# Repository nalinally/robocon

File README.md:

ロボコンで使ったプログラムまとめておきます！ <br>
使ったマイコン <br>
・Nucleo f303k8 <br>
・Jetson Nano <br>
2021NHKfinal と 2021NHK がありますが、たぶん最新版は 2021NHK です

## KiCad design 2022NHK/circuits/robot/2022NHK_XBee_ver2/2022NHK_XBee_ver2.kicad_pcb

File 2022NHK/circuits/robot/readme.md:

# ロボットに乗せた回路です

たぶんいらないファイル(発注するために生成したやつとか)がたくさん入ってて見にくくてすみません

・2022NHK_Include ... メイン基板です メイン基板は3枚ありますが全部これです

・2022NHK_Convert ... サーボ用の信号線(6V)を5Vに変換します

・2022NHK_Relay ... 遠隔非常停止(受信側)のリレーを取り換え可能な感じにしました　そのためにリレーをdip化したやつです

・2022NHK_Source ... Tコネクタからの電源を5Vに降圧してUSB電源にします。各1.5Aずつしか流せないので注意

・2022NHK_XBee_Ver2 ... ロボットに乗せる遠隔非常停止(受信側) フォトカプラでリレーを駆動してます 当社比一番かっこいい回路

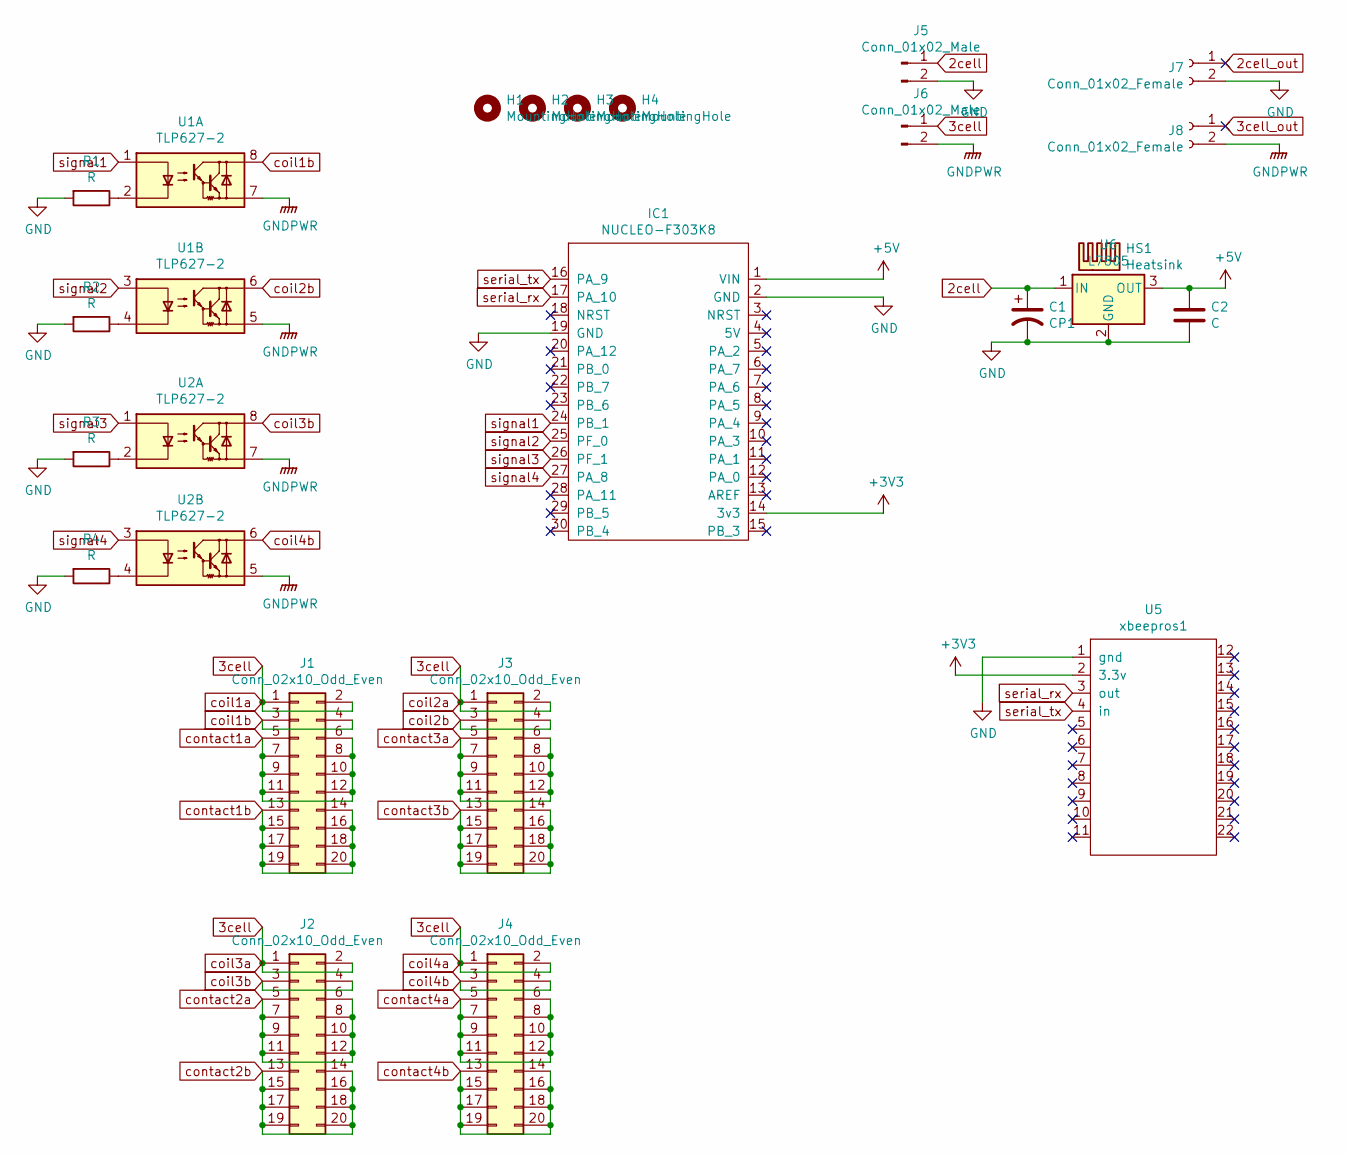
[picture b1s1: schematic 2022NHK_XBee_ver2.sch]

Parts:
C1: CP1; CP_Radial_D6.3mm_P2.50mm
C2: C; C_Disc_D4.7mm_W2.5mm_P5.00mm
H1, H2, H3, H4: MountingHole; MountingHole_3.2mm_M3_DIN965_Pad
HS1: Heatsink; Heatsink1
IC1: NUCLEO-F303K8
J1, J2, J3, J4: Conn_02x10_Odd_Even; PinSocket_2x10_P2.54mm_Vertical
J5, J6: Conn_01x02_Male; Connector_T_Male
J7, J8: Conn_01x02_Female; Connector_T_Female
R1, R2, R3, R4: R; R_Axial_DIN0309_L9.0mm_D3.2mm_P15.24mm_Horizontal
U1, U2: TLP627-2; DIP-8_W7.62mm
U5: xbeepros1; xbee_pro_s1
U6: L7805; TO-220F-3_Vertical

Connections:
2cell: C1.1, J5.1, U6.1 (IN)
2cell_out: J7.1
3cell: J1.1, J1.2, J2.1, J2.2, J3.1, J3.2, J4.1, J4.2, J6.1
3cell_out: J8.1
+3V3: IC1.14 (3v3), U5.2 (3.3v)
+5V: C2.1, IC1.1 (VIN), U6.3 (OUT)
GND: C1.2, C2.2, IC1.2 (GND), IC1.19 (GND), J5.2, J7.2, R1.2, R2.2, R3.2, R4.2, U5.1 (gnd), U6.2 (GND)
GNDPWR: J6.2, J8.2, U1.5, U1.7, U2.5, U2.7
unnamed: R1.1, U1.2
unnamed: R2.1, U1.4
unnamed: R3.1, U2.2
unnamed: R4.1, U2.4
coil1b: J1.3, J1.4, U1.8
coil2b: J3.3, J3.4, U1.6
coil3b: J2.3, J2.4, U2.8
coil4b: J4.3, J4.4, U2.6
contact1a: J1.5, J1.6, J1.7, J1.8, J1.9, J1.10, J1.11, J1.12
contact1b: J1.13, J1.14, J1.15, J1.16, J1.17, J1.18, J1.19, J1.20
contact2a: J2.5, J2.6, J2.7, J2.8, J2.9, J2.10, J2.11, J2.12
contact2b: J2.13, J2.14, J2.15, J2.16, J2.17, J2.18, J2.19, J2.20
contact3a: J3.5, J3.6, J3.7, J3.8, J3.9, J3.10, J3.11, J3.12
contact3b: J3.13, J3.14, J3.15, J3.16, J3.17, J3.18, J3.19, J3.20
contact4a: J4.5, J4.6, J4.7, J4.8, J4.9, J4.10, J4.11, J4.12
contact4b: J4.13, J4.14, J4.15, J4.16, J4.17, J4.18, J4.19, J4.20
serial_rx: IC1.17 (PA_10), U5.3 (out)
serial_tx: IC1.16 (PA_9), U5.4 (in)
signal1: IC1.24 (PB_1), U1.1
signal2: IC1.25 (PF_0), U1.3
signal3: IC1.26 (PF_1), U2.1
signal4: IC1.27 (PA_8), U2.3

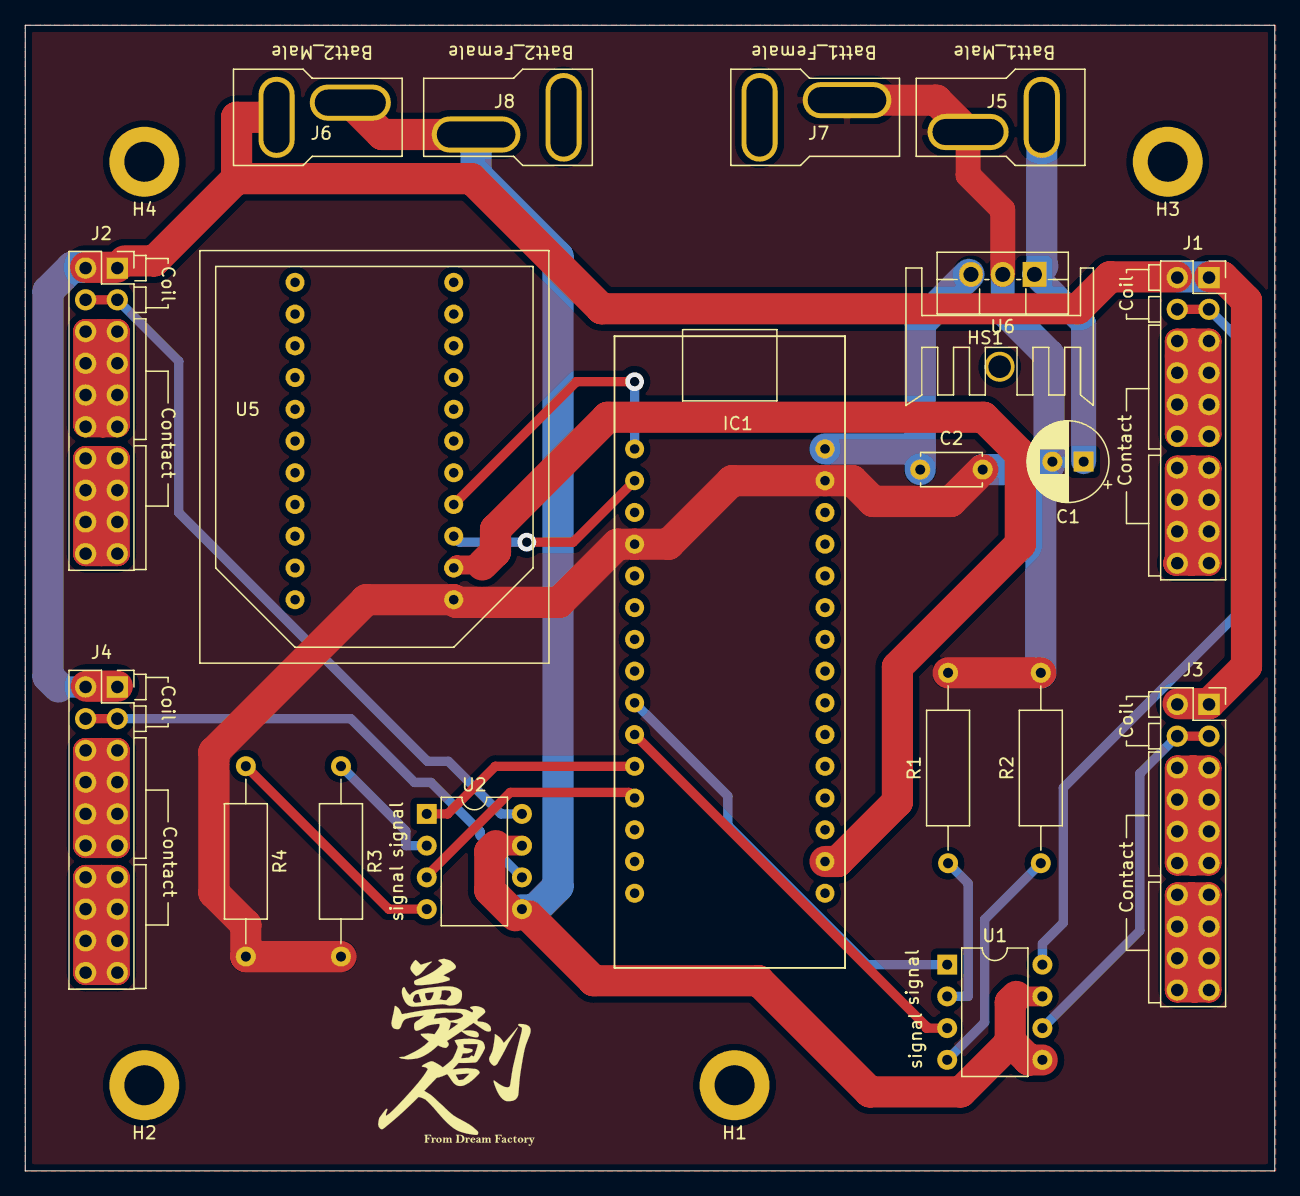
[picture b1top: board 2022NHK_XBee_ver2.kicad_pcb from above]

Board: 2 copper layers, 100.0 x 91.7 mm, 24 parts (0 on the bottom side), 28 nets.

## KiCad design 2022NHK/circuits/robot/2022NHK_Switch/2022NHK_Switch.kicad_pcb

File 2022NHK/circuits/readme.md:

# 回路がいるよ

controller ... コントローラに乗せる回路

robot ... ロボットに乗せる回路

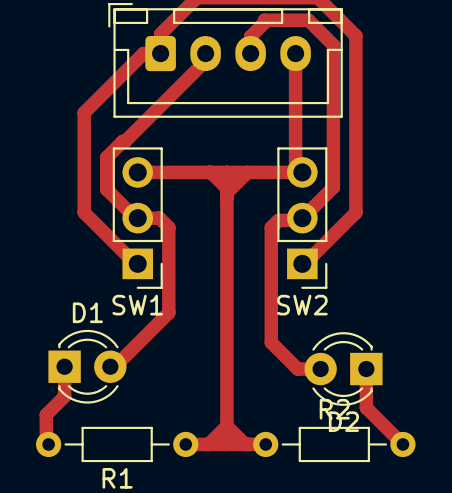
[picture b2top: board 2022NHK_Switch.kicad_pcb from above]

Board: 2 copper layers, 7 parts (0 on the bottom side), 6 nets.

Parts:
D1, D2: LED; LED_D3.0mm
J1: Conn_01x04_Male; JST_XH_B4B-XH-A_1x04_P2.50mm_Vertical
R1, R2: R; R_Axial_DIN0204_L3.6mm_D1.6mm_P7.62mm_Horizontal
SW1, SW2: SW_DPDT_x2; PinHeader_1x03_P2.54mm_Vertical

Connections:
5v: J1.1, SW1.1, SW2.1
GND: J1.4, R1.1, R2.1, SW1.3, SW2.3
unnamed: D1.1, R1.2
unnamed: D2.1, R2.2
out1: D1.2, J1.2, SW1.2
out2: D2.2, J1.3, SW2.2

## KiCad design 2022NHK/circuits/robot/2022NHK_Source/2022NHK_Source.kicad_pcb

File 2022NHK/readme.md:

# 2022年NHKロボコン(紙飛行機のやつ)のロボットの回路とプログラムを乗せます

circuits ... 回路

sources ... プログラム

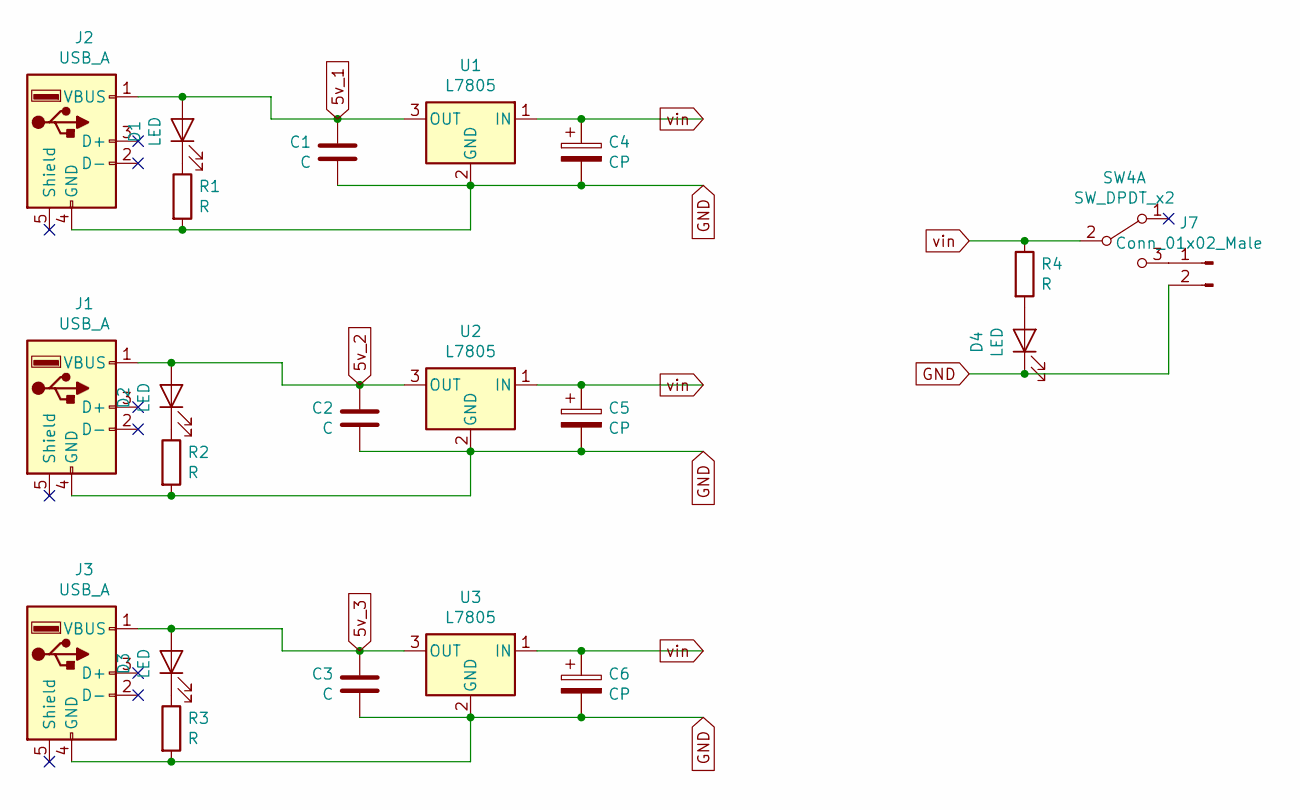
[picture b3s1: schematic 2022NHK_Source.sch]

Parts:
C1, C2, C3: C; C_Disc_D4.7mm_W2.5mm_P5.00mm
C4, C5, C6: CP; CP_Radial_D6.3mm_P2.50mm
D1, D2, D3, D4: LED; LED_D3.0mm
J1, J2, J3: USB_A; USB_A_Wuerth_61400826021_Horizontal_Stacked
J7: Conn_01x02_Male; Connector_T_Male
R1, R2, R3, R4: R; R_Axial_DIN0207_L6.3mm_D2.5mm_P7.62mm_Horizontal
SW4: SW_DPDT_x2; PinHeader_1x03_P2.54mm_Vertical
U1, U2, U3: L7805; TO-220F-3_Vertical

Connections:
5v_1: C1.1, D1.2 (A), J2.1 (VBUS), U1.3 (OUT)
5v_2: C2.1, D2.2 (A), J1.1 (VBUS), U2.3 (OUT)
5v_3: C3.1, D3.2 (A), J3.1 (VBUS), U3.3 (OUT)
GND: C1.2, C2.2, C3.2, C4.2, C5.2, C6.2, D4.1 (K), J1.4 (GND), J2.4 (GND), J3.4 (GND), J7.2, R1.2, R2.2, R3.2, U1.2 (GND), U2.2 (GND), U3.2 (GND)
unnamed: D1.1 (K), R1.1
unnamed: D2.1 (K), R2.1
unnamed: D3.1 (K), R3.1
unnamed: D4.2 (A), R4.2
unnamed: J7.1, SW4.3 (C)
vin: C4.1, C5.1, C6.1, R4.1, SW4.2 (B), U1.1 (IN), U2.1 (IN), U3.1 (IN)

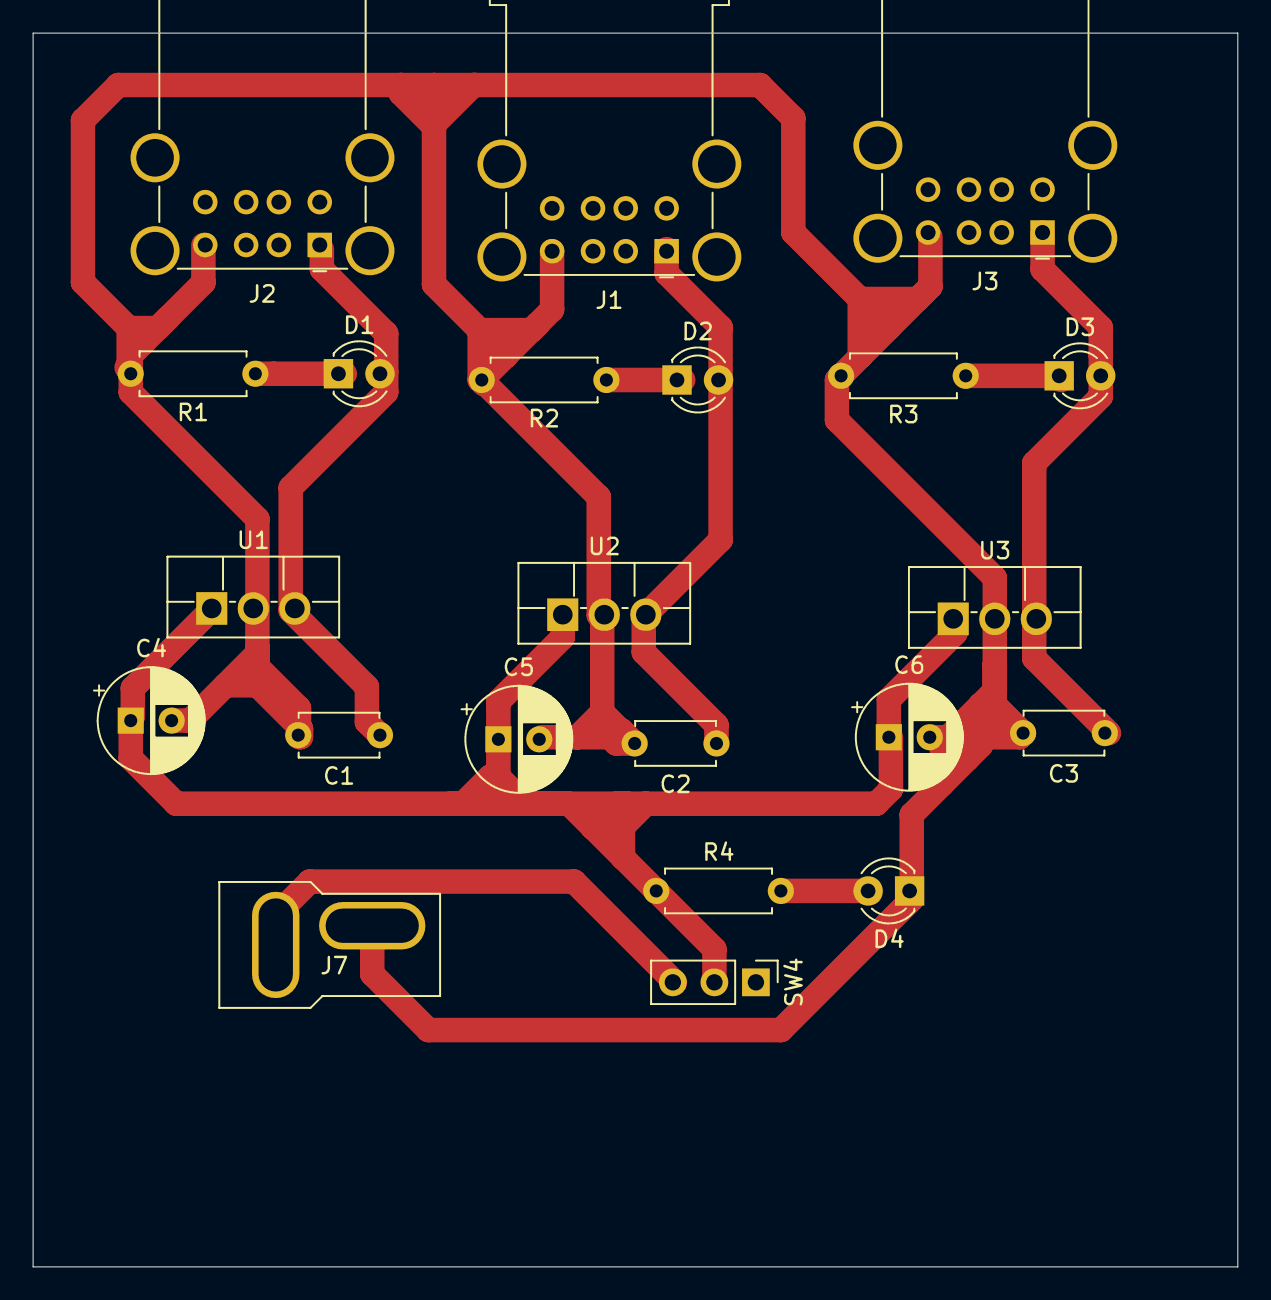
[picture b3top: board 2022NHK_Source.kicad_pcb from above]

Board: 2 copper layers, 73.7 x 75.4 mm, 22 parts (0 on the bottom side), 10 nets.

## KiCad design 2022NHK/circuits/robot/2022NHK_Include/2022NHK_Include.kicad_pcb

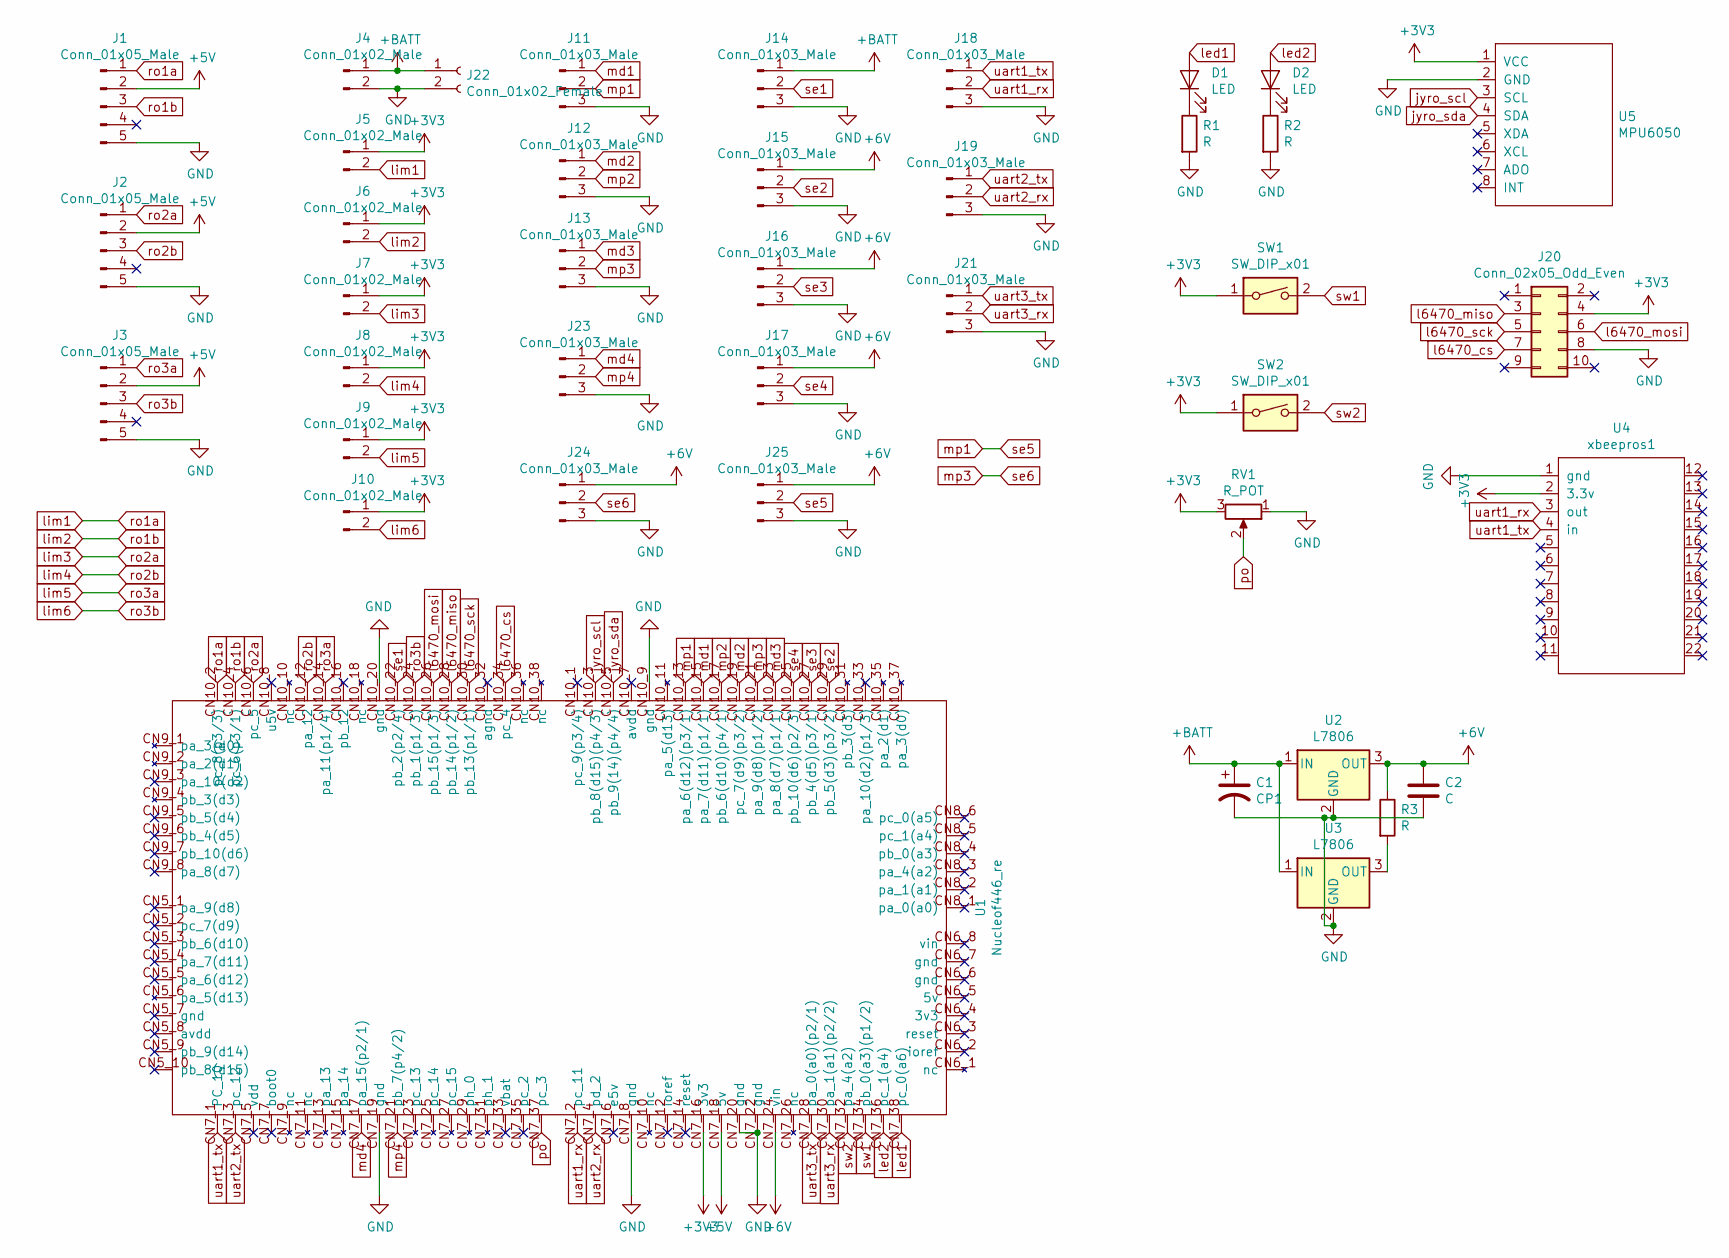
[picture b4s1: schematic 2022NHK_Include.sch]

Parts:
C1: CP1; CP_Radial_D7.5mm_P2.50mm
C2: C; C_Axial_L3.8mm_D2.6mm_P7.50mm_Horizontal
D1, D2: LED; LED_D3.0mm
J1, J2, J3: Conn_01x05_Male; JST_XH_B5B-XH-A_1x05_P2.50mm_Vertical
J4: Conn_01x02_Male; Connector_T_Male
J5, J6, J7, J8, J9, J10: Conn_01x02_Male; JST_XH_S2B-XH-A_1x02_P2.50mm_Horizontal
J11, J12, J13, J14, J15, J16, J17, J23: Conn_01x03_Male; JST_XH_S3B-XH-A_1x03_P2.50mm_Horizontal
J18, J19, J21, J24, J25: Conn_01x03_Male; JST_XH_B3B-XH-A_1x03_P2.50mm_Vertical
J20: Conn_02x05_Odd_Even; PinHeader_2x05_P2.54mm_Vertical
J22: Conn_01x02_Female; Connector_T_Female
R1, R2, R3: R; R_Axial_DIN0204_L3.6mm_D1.6mm_P7.62mm_Horizontal
RV1: R_POT; Potentiometer_Bourns_PTV09A-1_Single_Vertical
SW1, SW2: SW_DIP_x01; SW_Toggle_2.54mm
U1: Nucleof446_re; MODULE_NUCLEO_F446RE
U2, U3: L7806; NJM7805FA
U4: xbeepros1; xbee_pro_s1
U5: MPU6050; GY=521

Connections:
+3V3: J5.1, J6.1, J7.1, J8.1, J9.1, J10.1, J20.4, RV1.3, SW1.1, SW2.1, U1.CN7_16 (3v3), U4.2 (3.3v), U5.1 (VCC)
+5V: J1.2, J2.2, J3.2, U1.CN7_18 (5v)
+6V: C2.1, J15.1, J16.1, J17.1, J24.1, J25.1, R3.1, U1.CN7_24 (vin), U2.3 (OUT)
+BATT: C1.1, J4.1, J14.1, J22.1, U2.1 (IN), U3.1 (IN)
GND: C1.2, C2.2, J1.5, J2.5, J3.5, J4.2, J11.3, J12.3, J13.3, J14.3, J15.3, J16.3, J17.3, J18.3, J19.3, J20.8, J21.3, J22.2, J23.3, J24.3, J25.3, R1.2, R2.2, RV1.1, U1.CN7_8 (gnd), U1.CN7_19 (gnd), U1.CN7_20 (gnd), U1.CN7_22 (gnd), U1.CN10_9 (gnd), U1.CN10_20 (gnd), U2.2 (GND), U3.2 (GND), U4.1 (gnd), U5.2 (GND)
unnamed: D1.1 (K), R1.1
unnamed: D2.1 (K), R2.1
unnamed: R3.2, U3.3 (OUT)
jyro_scl: U1.CN10_3 (pb_8(d15)(p4/3)), U5.3 (SCL)
jyro_sda: U1.CN10_5 (pb_9(14)(p4/4)), U5.4 (SDA)
l6470_cs: J20.7, U1.CN10_34 (pc_4)
l6470_miso: J20.3, U1.CN10_28 (pb_14(p1/2))
l6470_mosi: J20.6, U1.CN10_26 (pb_15(p1/3))
l6470_sck: J20.5, U1.CN10_30 (pb_13(p1/1))
led1: D1.2 (A), U1.CN7_38 (pc_0(a6))
led2: D2.2 (A), U1.CN7_36 (pc_1(a4))
lim1: J1.1, J5.2, U1.CN10_2 (pc_8(p3/3))
lim2: J1.3, J6.2, U1.CN10_4 (pc_6(p3/1))
lim3: J2.1, J7.2, U1.CN10_6 (pc_5)
lim4: J2.3, J8.2, U1.CN10_12 (pa_12)
lim5: J3.1, J9.2, U1.CN10_14 (pa_11(p1/4))
lim6: J3.3, J10.2, U1.CN10_24 (pb_1(p1/3))
md1: J11.1, U1.CN10_15 (pa_7(d11)(p1/1))
md2: J12.1, U1.CN10_19 (pc_7(d9)(p3/2))
md3: J13.1, U1.CN10_23 (pa_8(d7)(p1/1))
md4: J23.1, U1.CN7_17 (pa_15(p2/1))
mp1: J11.2, J25.2, U1.CN10_13 (pa_6(d12)(p3/1))
mp2: J12.2, U1.CN10_17 (pb_6(d10)(p4/1))
mp3: J13.2, J24.2, U1.CN10_21 (pa_9(d8)(p1/2))
mp4: J23.2, U1.CN7_21 (pb_7(p4/2))
po: RV1.2, U1.CN7_37 (pc_3)
se1: J14.2, U1.CN10_22 (pb_2(p2/4))
se2: J15.2, U1.CN10_29 (pb_5(d3)(p3/2))
se3: J16.2, U1.CN10_27 (pb_4(d5)(p3/1))
se4: J17.2, U1.CN10_25 (pb_10(d6)(p2/3))
sw1: SW1.2, U1.CN7_34 (pb_0(a3)(p1/2))
sw2: SW2.2, U1.CN7_32 (pa_4(a2))
uart1_rx: J18.2, U1.CN7_2 (pc_11), U4.3 (out)
uart1_tx: J18.1, U1.CN7_1 (PC_10), U4.4 (in)
uart2_rx: J19.2, U1.CN7_4 (pd_2)
uart2_tx: J19.1, U1.CN7_3 (pc_12)
uart3_rx: J21.2, U1.CN7_30 (pa_1(a1)(p2/2))
uart3_tx: J21.1, U1.CN7_28 (pa_0(a0)(p2/1))

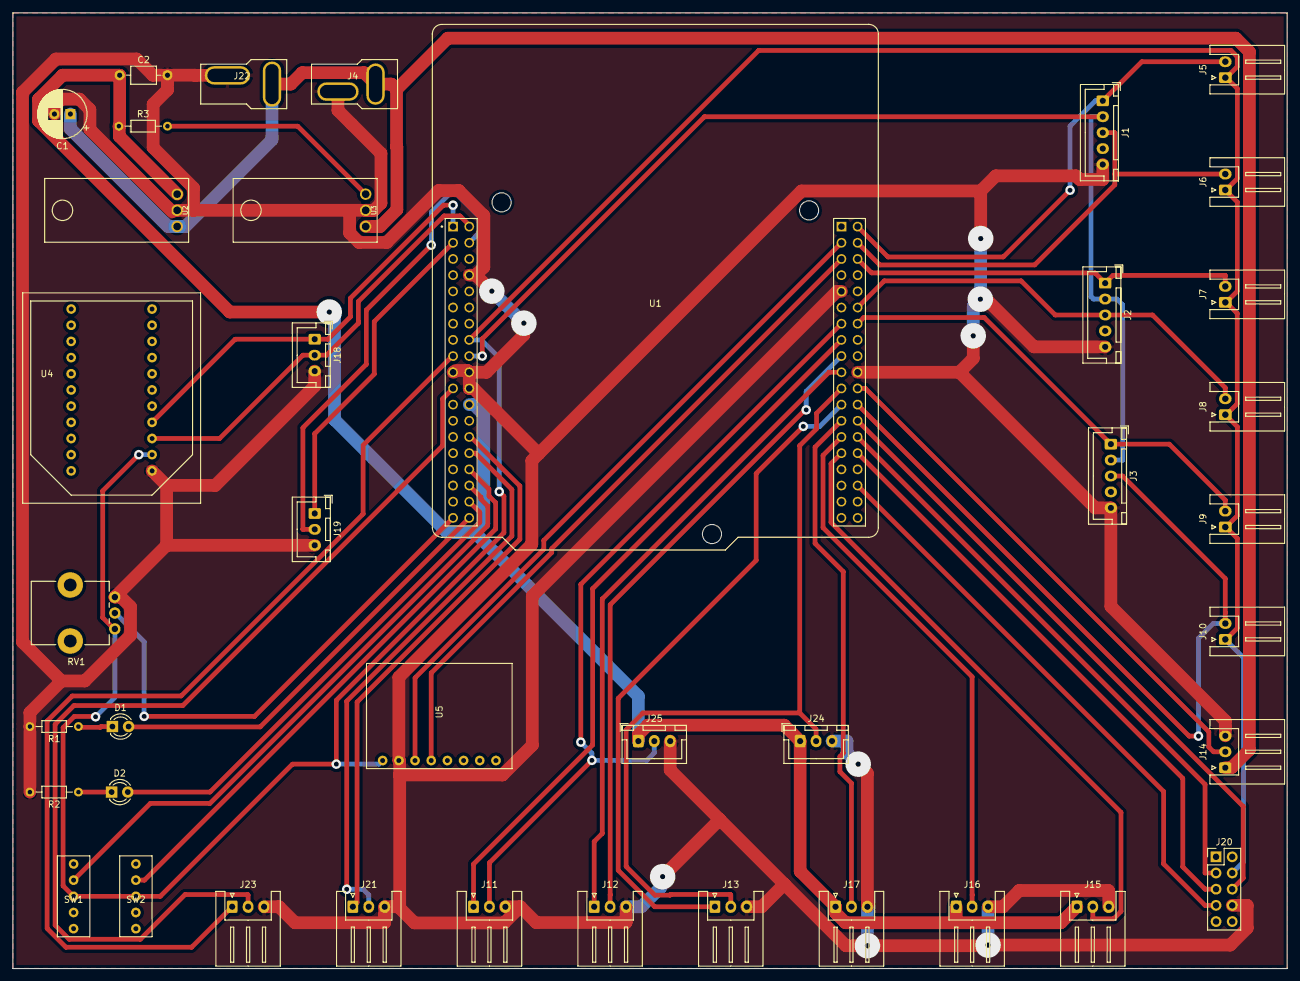
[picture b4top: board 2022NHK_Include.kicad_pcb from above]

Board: 2 copper layers, 200.0 x 150.0 mm, 40 parts (0 on the bottom side), 43 nets.

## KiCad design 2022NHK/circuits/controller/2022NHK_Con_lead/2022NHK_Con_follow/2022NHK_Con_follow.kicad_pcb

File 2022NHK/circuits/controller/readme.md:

# コントローラに乗せる用の回路です

・2022NHK_Con_Lead ... 親機基板

・2022NHK_Con_Follow ... 子機基板

・2022NHK_Switch ... 右手、左手の動かすかどうかの切り替え基板

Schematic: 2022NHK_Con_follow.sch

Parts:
C1: CP1; CP_Radial_D6.3mm_P2.50mm
C2: C; C_Disc_D4.3mm_W1.9mm_P5.00mm
D1: LED; LED_D3.0mm
IC1: NUCLEO-F303K8
J2, J5, J6, J8, J9, J10: Conn_01x05_Male; JST_XH_S5B-XH-A_1x05_P2.50mm_Horizontal
J3: Conn_01x02_Male; Connector_T_Male
J4: Conn_01x02_Female; Connector_T_Female
J7: Conn_01x03_Male; JST_XH_S3B-XH-A_1x03_P2.50mm_Horizontal
J11: Conn_01x02_Male; JST_XH_S2B-XH-A_1x02_P2.50mm_Horizontal
R1: R; R_Axial_DIN0204_L3.6mm_D1.6mm_P7.62mm_Horizontal
U1: L7805; NJM7805FA

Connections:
2a: IC1.20, J5.3
2b: IC1.27, J5.1
3a: IC1.28, J8.3
3b: IC1.12, J8.1
4a: IC1.6, J2.3
4b: IC1.7, J2.1
5a: IC1.8, J6.3
5b: IC1.9, J6.1
5v_in: C2.1, IC1.1, U1.3 (OUT)
5v_out: IC1.4, J2.2, J5.2, J6.2, J8.2, J9.2
6a: IC1.10, J9.3
6b: IC1.11, J9.1
+3V3: IC1.14, J10.1
+BATT: C1.1, J3.1, J4.1, U1.1 (IN)
GND: C1.2, C2.2, IC1.2, IC1.19, J2.5, J3.2, J4.2, J5.5, J6.5, J7.3, J8.5, J9.5, J10.2, J11.2, R1.2, U1.2 (GND)
unnamed: D1.1 (K), R1.1
bt1: IC1.29, J10.3
bt2: IC1.30, J10.4
bt3: IC1.15, J10.5
led1: D1.2 (A), IC1.24, J11.1
uart_rx: IC1.17, IC1.22, J7.2
uart_tx: IC1.16, IC1.23, J7.1

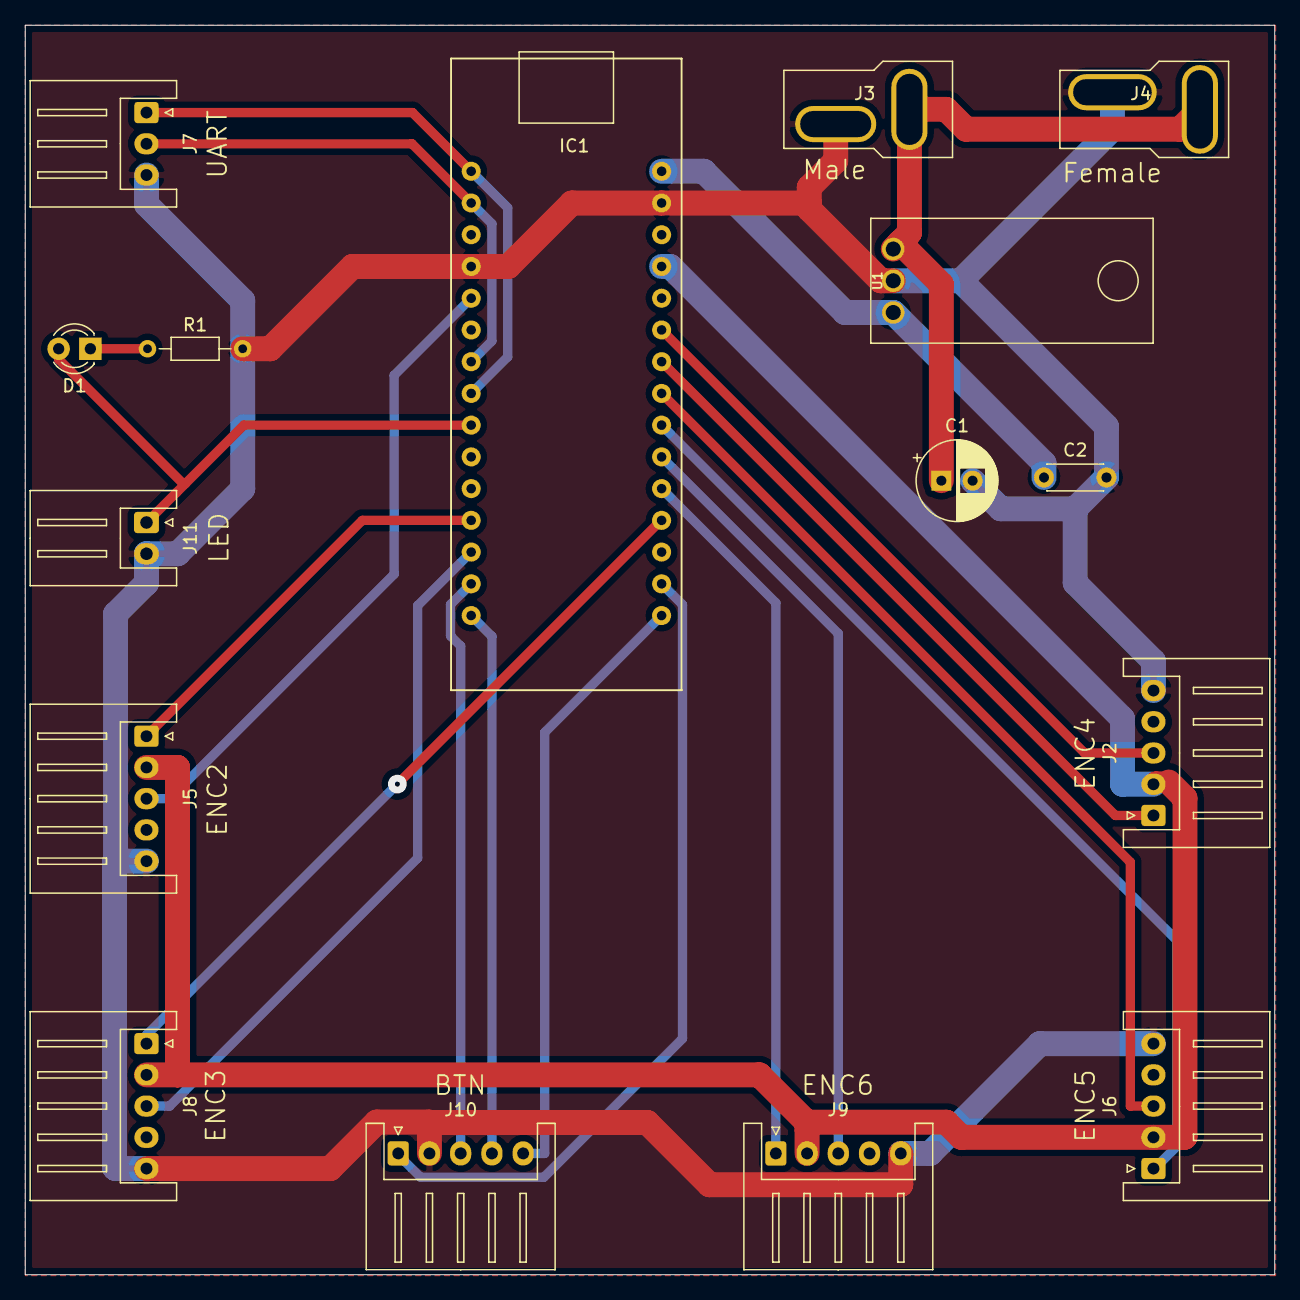
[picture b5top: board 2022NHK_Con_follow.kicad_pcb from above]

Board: 2 copper layers, 100.0 x 100.0 mm, 16 parts (0 on the bottom side), 22 nets.

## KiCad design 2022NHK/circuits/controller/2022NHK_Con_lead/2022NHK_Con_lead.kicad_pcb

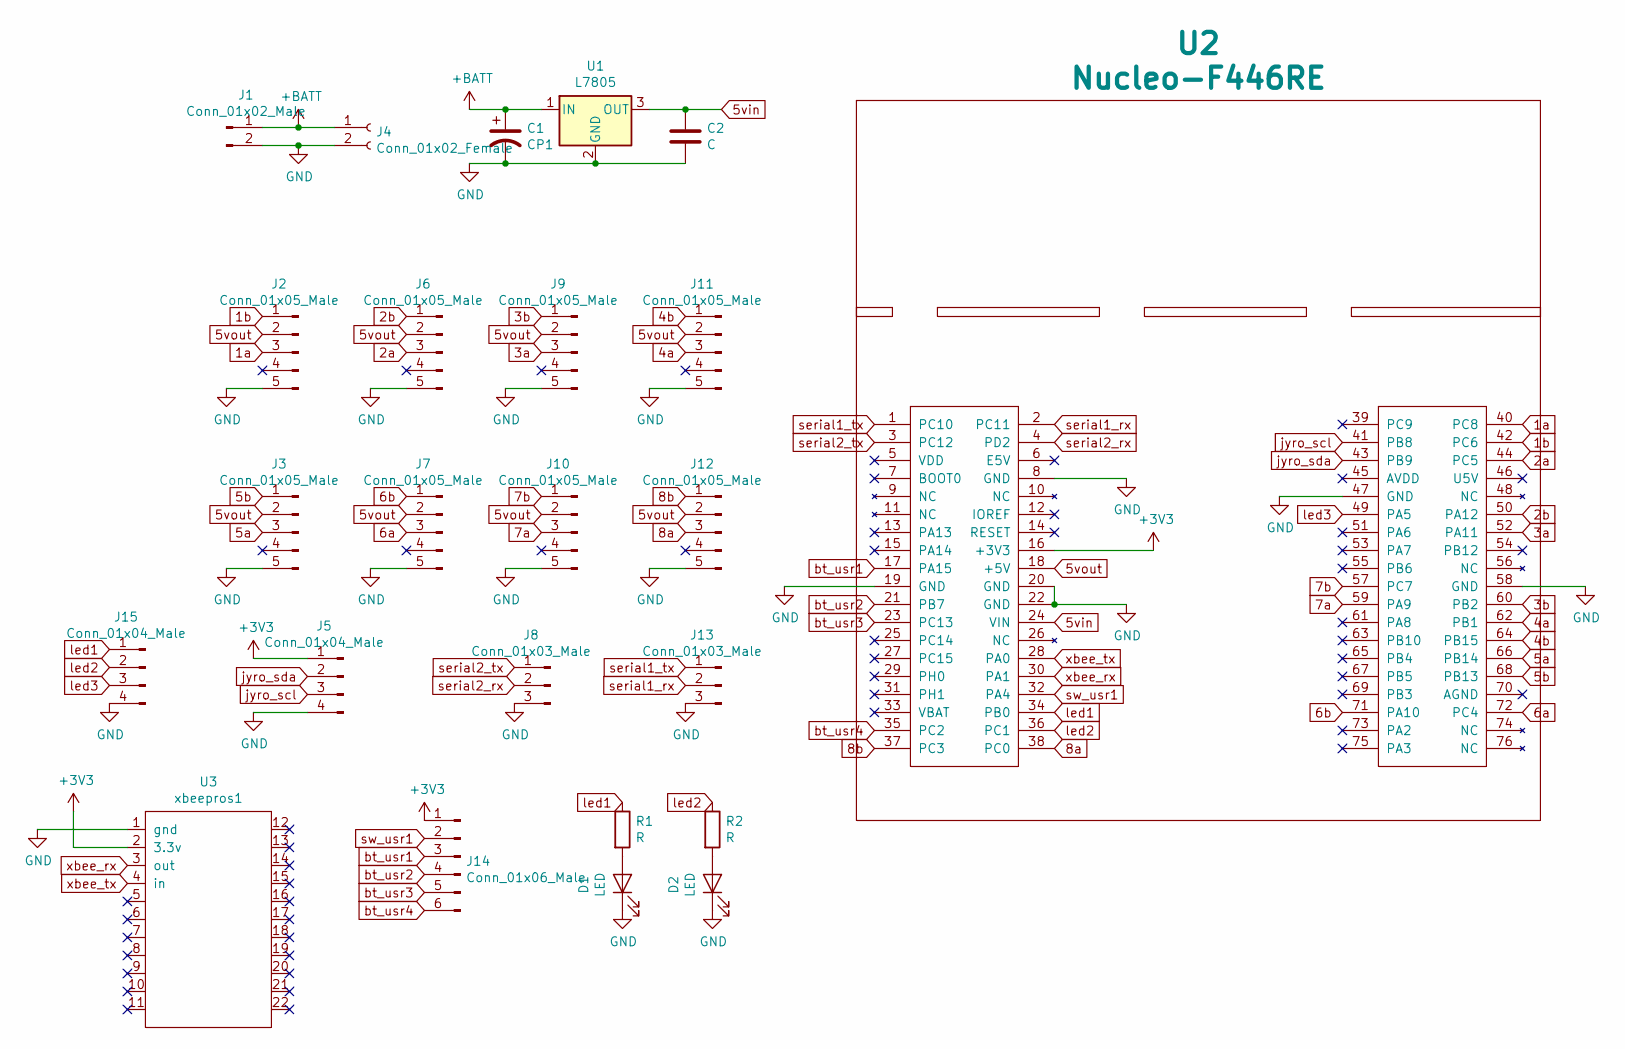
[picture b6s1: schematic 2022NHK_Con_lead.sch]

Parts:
C1: CP1; CP_Radial_D6.3mm_P2.50mm
C2: C; C_Axial_L3.8mm_D2.6mm_P7.50mm_Horizontal
D1, D2: LED; LED_D3.0mm
J1: Conn_01x02_Male; Connector_T_Male
J2, J3, J6, J7, J9, J10, J11, J12: Conn_01x05_Male; JST_XH_S5B-XH-A_1x05_P2.50mm_Horizontal
J4: Conn_01x02_Female; Connector_T_Female
J5, J15: Conn_01x04_Male; JST_XH_S4B-XH-A_1x04_P2.50mm_Horizontal
J8, J13: Conn_01x03_Male; JST_XH_S3B-XH-A_1x03_P2.50mm_Horizontal
J14: Conn_01x06_Male; JST_XH_S6B-XH-A_1x06_P2.50mm_Horizontal
R1, R2: R; R_Axial_DIN0204_L3.6mm_D1.6mm_P7.62mm_Horizontal
U1: L7805; NJM7805FA
U2: Nucleo-F446RE; MODULE_NUCLEO_F446RE
U3: xbeepros1; xbee_pro_s1

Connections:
1a: J2.3, U2.40 (PC8)
1b: J2.1, U2.42 (PC6)
2a: J6.3, U2.44 (PC5)
2b: J6.1, U2.50 (PA12)
3a: J9.3, U2.52 (PA11)
3b: J9.1, U2.60 (PB2)
4a: J11.3, U2.62 (PB1)
4b: J11.1, U2.64 (PB15)
5a: J3.3, U2.66 (PB14)
5b: J3.1, U2.68 (PB13)
5vin: C2.1, U1.3 (OUT), U2.24 (VIN)
5vout: J2.2, J3.2, J6.2, J7.2, J9.2, J10.2, J11.2, J12.2, U2.18 (+5V)
6a: J7.3, U2.72 (PC4)
6b: J7.1, U2.71 (PA10)
7a: J10.3, U2.59 (PA9)
7b: J10.1, U2.57 (PC7)
8a: J12.3, U2.38 (PC0)
8b: J12.1, U2.37 (PC3)
+3V3: J5.1, J14.1, U2.16 (+3V3), U3.2 (3.3v)
+BATT: C1.1, J1.1, J4.1, U1.1 (IN)
GND: C1.2, C2.2, D1.1 (K), D2.1 (K), J1.2, J2.5, J3.5, J4.2, J5.4, J6.5, J7.5, J8.3, J9.5, J10.5, J11.5, J12.5, J13.3, J15.4, U1.2 (GND), U2.8 (GND), U2.19 (GND), U2.20 (GND), U2.22 (GND), U2.47 (GND), U2.58 (GND), U3.1 (gnd)
unnamed: D1.2 (A), R1.2
unnamed: D2.2 (A), R2.2
bt_usr1: J14.3, U2.17 (PA15)
bt_usr2: J14.4, U2.21 (PB7)
bt_usr3: J14.5, U2.23 (PC13)
bt_usr4: J14.6, U2.35 (PC2)
jyro_scl: J5.3, U2.41 (PB8)
jyro_sda: J5.2, U2.43 (PB9)
led1: J15.1, R1.1, U2.34 (PB0)
led2: J15.2, R2.1, U2.36 (PC1)
led3: J15.3, U2.49 (PA5)
serial1_rx: J13.2, U2.2 (PC11)
serial1_tx: J13.1, U2.1 (PC10)
serial2_rx: J8.2, U2.4 (PD2)
serial2_tx: J8.1, U2.3 (PC12)
sw_usr1: J14.2, U2.32 (PA4)
xbee_rx: U2.30 (PA1), U3.3 (out)
xbee_tx: U2.28 (PA0), U3.4 (in)

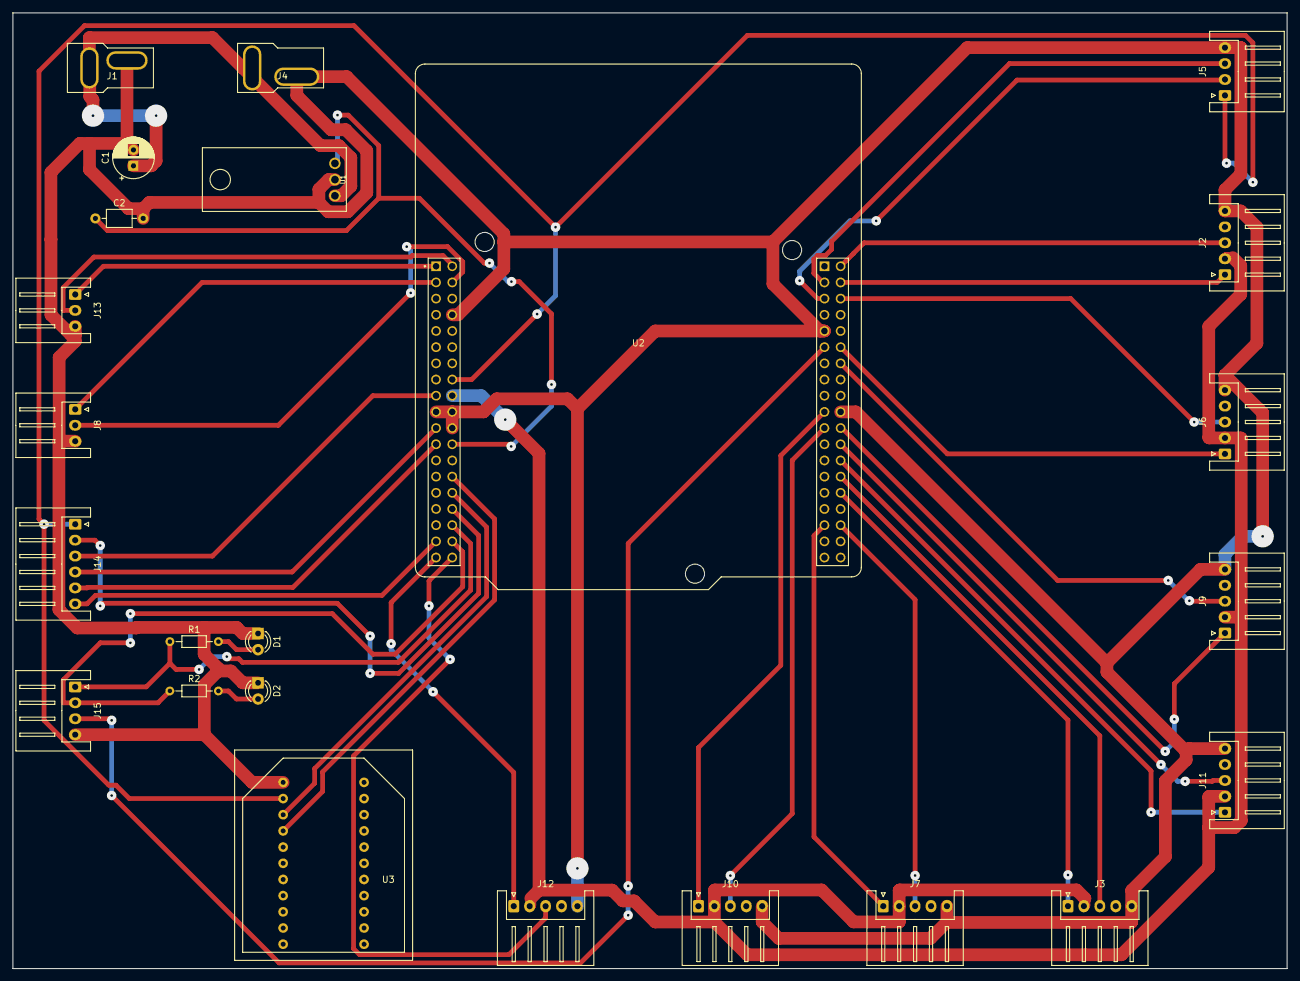
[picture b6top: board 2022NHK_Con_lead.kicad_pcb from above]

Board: 2 copper layers, 200.0 x 150.0 mm, 24 parts (0 on the bottom side), 39 nets.

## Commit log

2021-07-18 Create JetSonNanoセットアップメモ
2021-07-23 Create opencv_raspi
2021-10-24 change folder name
2022-11-28 Create dammy
2022-11-29 Rename readmed.md to readme.md
